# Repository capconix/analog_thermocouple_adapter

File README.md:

# analog_thermocouple_adapter
ATA or Analog Thermocouple Adapter - A simple K(or J) type thermocouple adapter with field-reconfigurable/disableable voltage offset for negative temps.

At this time, this is an untested design. I will update this README after I have done more testing.

License : This project is currently a hardware-only open source project. The contents of this repository is released under the CERN OHL version 1.2. If the project comes to include a software component, that component of this project will be licensed as necessary at that time.

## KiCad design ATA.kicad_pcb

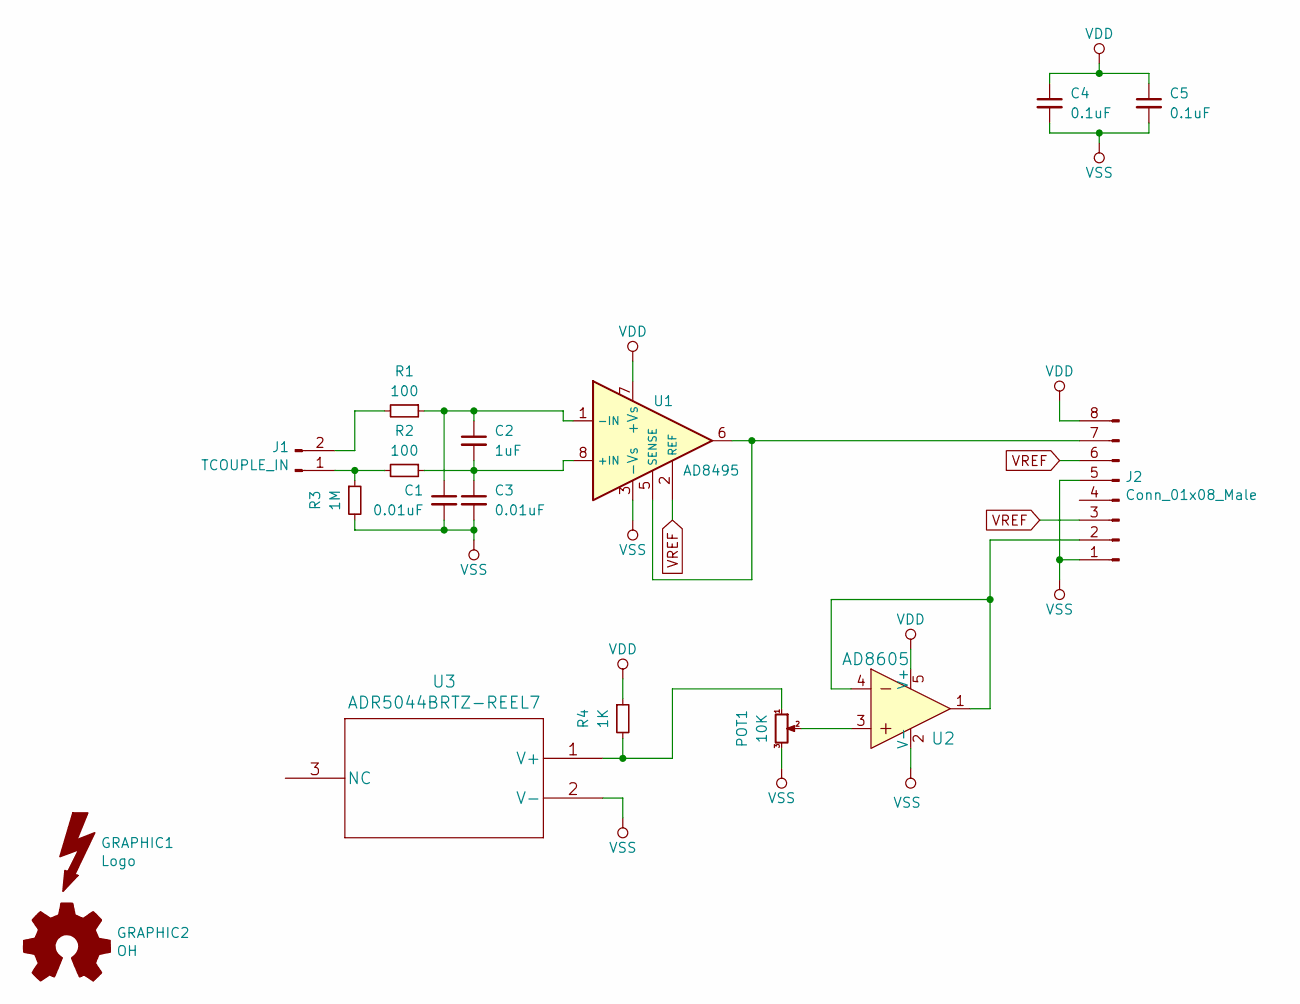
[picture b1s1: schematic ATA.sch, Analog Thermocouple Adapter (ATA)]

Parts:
C1, C3: 0.01uF; C_0603_1608Metric
C2: 1uF; C_0603_1608Metric
C4, C5: 0.1uF; C_0603_1608Metric
GRAPHIC1: Logo; CapConiX_Logo_10_7
GRAPHIC2: OH; OSHW-Logo_5.7x6mm_SilkScreen
J1: TCOUPLE_IN; SMD_H_2X
J2: Conn_01x08_Male; 0559350810_right_angle_8pos
POT1: 10K; 89PR
R1, R2: 100; R_0603_1608Metric
R3: 1M; R_0603_1608Metric
R4: 1K; R_0603_1608Metric
U1: AD8495; MSOP-8_3x3mm_P0.65mm
U2: AD8605; SOT-753; MPN AD8605ARTZ-REEL7; Digi-Key_PN AD8605ARTZREEL7CT-ND
U3: ADR5044BRTZ-REEL7; SOT-23

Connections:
unnamed: C1.1, C2.1, R1.1, U1.1 (-IN)
unnamed: C2.2, C3.1, R2.1, U1.8 (+IN)
unnamed: J1.1, R2.2, R3.1
unnamed: J1.2, R1.2
unnamed: J2.2, U2.1, U2.4
unnamed: J2.7, U1.5 (SENSE), U1.6
unnamed: POT1.1, R4.2, U3.1 (V+)
unnamed: POT1.2, U2.3
VDD: C4.1, C5.1, J2.8, R4.1, U1.7 (+Vs), U2.5 (V+)
VREF: J2.3, J2.6, U1.2 (REF)
VSS: C1.2, C3.2, C4.2, C5.2, J2.1, J2.5, POT1.3, R3.2, U1.3 (-Vs), U2.2 (V-), U3.2 (V-)

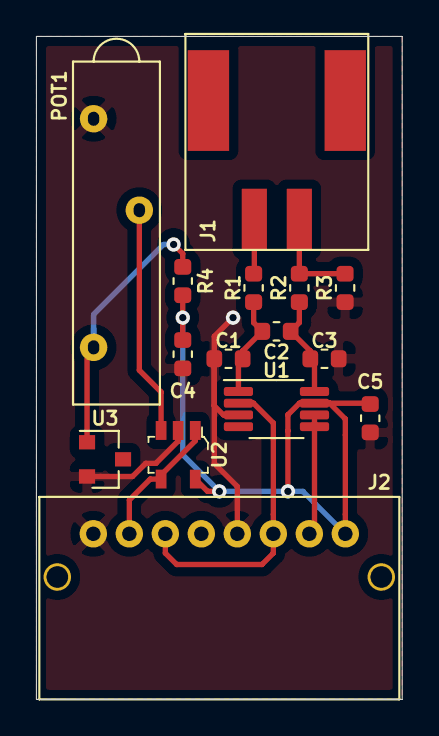
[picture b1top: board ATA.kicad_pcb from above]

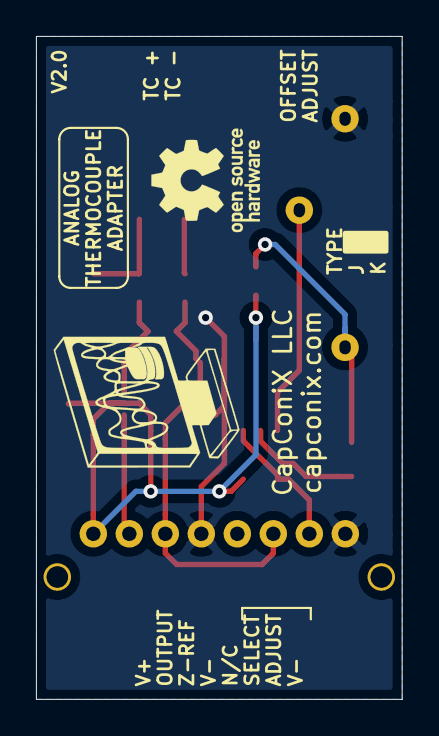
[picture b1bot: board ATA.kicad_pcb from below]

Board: 2 copper layers, 20.3 x 36.8 mm, 17 parts (2 on the bottom side), 11 nets.

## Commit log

2020-01-07 Updated license to include CERN OHL v1.2. GPLv3 was removed as this is a hardware-only project. If software needs to be added to this project, licensing will be updated for that new portion of the pr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
2020-01-07 Updated readme to include license statement
2020-01-07 Added project files to repository
2020-01-07 generated cam files for version 1.0 to be sent for manufacture
2020-01-22 Added voltage reference chip to high side of adjustable voltage divider reference
2020-01-22 Rearranged placement a bit. Generated CAM files for v2
